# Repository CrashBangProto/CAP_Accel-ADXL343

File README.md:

#Toadstool-Accel ADXL343

**Toadstool Cap - ADXL343 Accelerometer**

The Toadstool family is made up of breadboard-friendly prototyping boards that house a microcontroller, and modules called *Caps* that connect using a standard header.  The prototyping board is analagous to an Arduino/Launchpad and the Cap analagous to a shield/boosterpack.

This repository contains the schematics for the **Toadstool-Accel ADXL343 Cap**, a 3-axis Digital MEMS Accelerometer module that connects to  Toadstool prototyping boards using the common header.  The Analog Devices ADXL343 chip does all the work.

The boards were layed out using [KiCad](http://www.kicad-pcb.org) - KiCad is open source and awesome.

There are a number of other CrashBangProto respositories containing the schematics for other Toadstool boards and Caps, as well as sample code to get you up and running.

Visit the [Toadstool Webpages](http://www.crash-bang.com/projects/toadstool/) for more information on the project.

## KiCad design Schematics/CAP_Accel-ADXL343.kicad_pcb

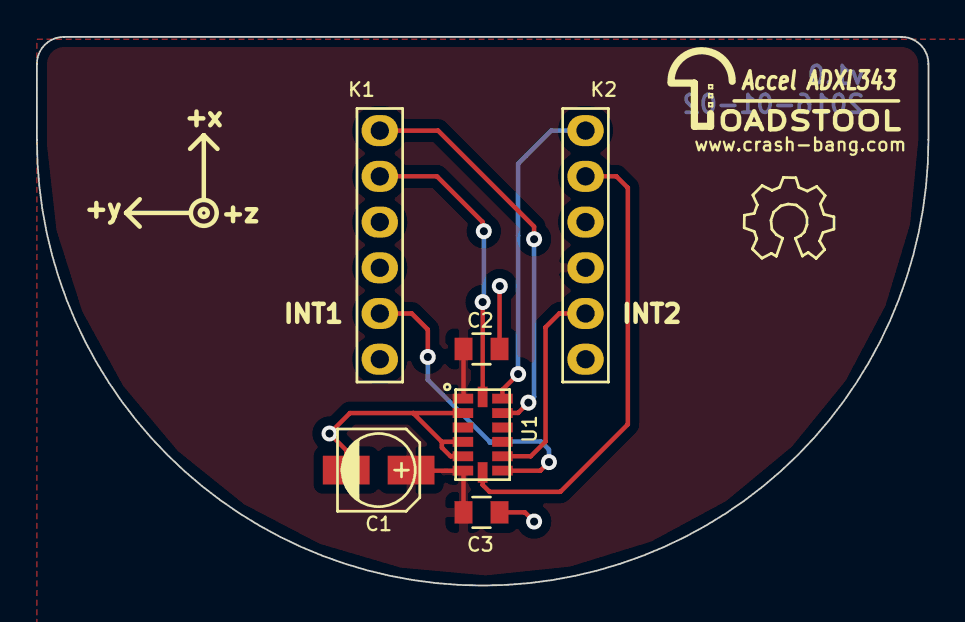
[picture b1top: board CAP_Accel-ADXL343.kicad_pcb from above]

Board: 2 copper layers, 49.5 x 30.5 mm, 7 parts (0 on the bottom side), 8 nets.

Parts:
C1: 10uF; c_elec_4x5.3
C2, C3: 0.1uF; C_0805
K1: CAP_CONN_LHS; Socket_Strip_Stackable_1x06
K2: CAP_CONN_RHS; Socket_Strip_Stackable_1x06
Toadstool_Logo: LOGO**; Toadstool_Logo
U1: ADXL343; ADXL343-LGA-14

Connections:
/MISO: K1.1, U1.12
/MOSI: K2.1, U1.13
/SCK: K1.2, U1.14
/SCL: K2.5, U1.9
/SDA: K1.5, U1.8
/SS1: K2.2, U1.7
GND: C1.2, C2.1, C3.2, K1.4, U1.2, U1.4, U1.5
VCC: C1.1, C2.2, C3.1, K2.4, U1.1, U1.6

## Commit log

2016-01-01 :tada: Added .gitattributes
2016-01-02 Silkscreen Changes
    Cosmetic changes - positioning, OSHW logo
    Labels for Int1 and Int2 pins
    New Gerbers generated
2016-01-02 Added Github Files
    Added Gitignore, Readme and License files
